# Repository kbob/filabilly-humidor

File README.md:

# FilaBilly Humidor

The FilaBilly Humidor (FBH) is a smart cabinet for 3D printer filament storage and humidity control.  It's based on an IKEA BILLY bookcase and contains an active dehumidifier.  It has lighting, environment sensors, and a display screen, and it is Internet enabled.

The FilaBilly Humidor is based on [ESPHome](https://esphome.io/).  It can be used as a standalone device or integrated into [Home Assistant](https://homeassistant.io/).

**Status:** Mostly vaporware.  Some materials have been acquired.

## FilaBilly Dehumidifier

The FilaBilly Dehumidifier (FBD) is the dehumidifier component.  It is a compact active dehumidifier that is also Internet enabled.  The FBD can also be used without the FBH, either standalone or directly integrated into Home Assistant.  The FBD also uses ESPHome.

**Status:** Designed, printed, tested.

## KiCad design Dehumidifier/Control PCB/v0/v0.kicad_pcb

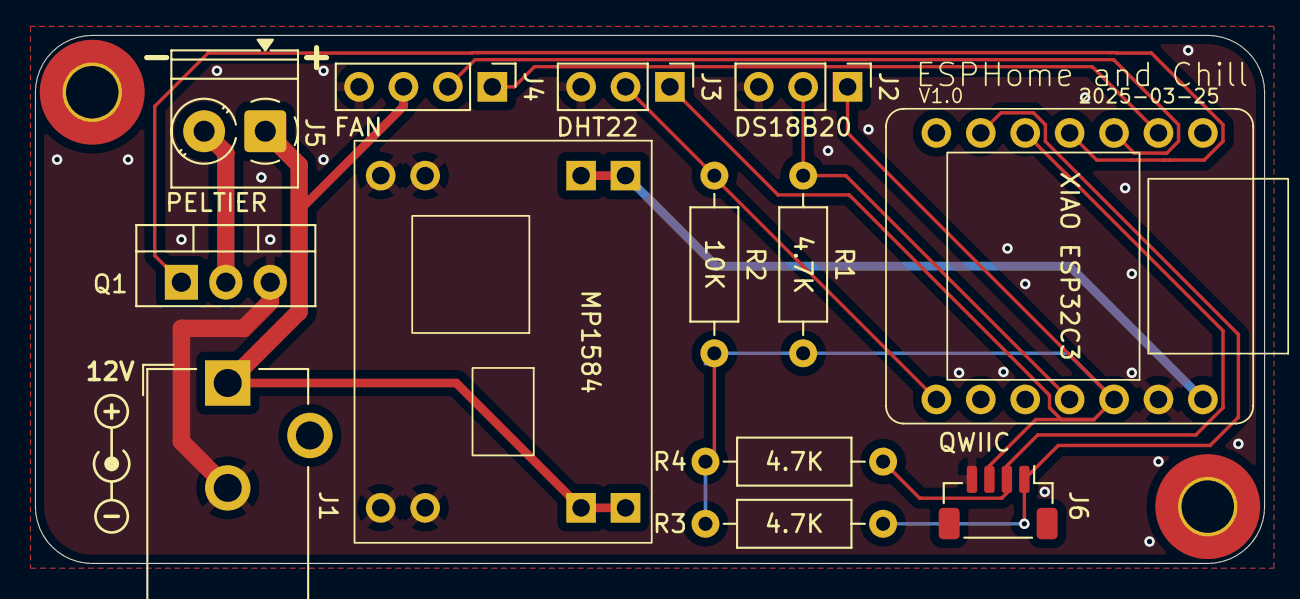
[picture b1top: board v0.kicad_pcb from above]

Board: 2 copper layers, 70.3 x 30.2 mm, 13 parts (0 on the bottom side), 12 nets.

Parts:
J1: Barrel_Jack; BarrelJack_CUI_PJ-102AH_Horizontal
J2, J3: 2.54mm Header; PinHeader_1x03_P2.54mm_Vertical
J4: 2.54mm Header; PinHeader_1x04_P2.54mm_Vertical
J5: Screw Term; TerminalBlock_Phoenix_PT-1,5-2-3.5-H_1x02_P3.50mm_Horizontal
J6: QWIIC; JST_SH_BM04B-SRSS-TB_1x04-1MP_P1.00mm_Vertical
Q1: IRLB8721PBF; TO-220-3_Vertical
R1, R3, R4: 4.7K; R_Axial_DIN0207_L6.3mm_D2.5mm_P10.16mm_Horizontal
R2: 10K; R_Axial_DIN0207_L6.3mm_D2.5mm_P10.16mm_Horizontal
U1: XIAO ESP32C3; XIAO_on_Sockets
U2: MP1584; MP1584_PCB

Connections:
+3.3V: J2.1, J3.1, J6.3, R1.1, R2.1, R3.1, R4.1, U1.12 (VCC_3V3)
+5V: U1.14 (VUSB), U2.7 (OUT+), U2.8 (OUT+)
+12V: J1.1, J4.3, J5.1, U2.1 (IN+), U2.2 (IN+)
GND: J1.2, J2.3, J3.3, J4.4, J6.4, Q1.3 (S), U1.13 (GND), U2.3 (IN-), U2.4 (IN-), U2.5 (OUT-), U2.6 (OUT-)
GPIO3/FAN_PWM: J4.1, U1.2 (D1)
GPIO4/FAN_TACH: J4.2, U1.3 (D2)
GPIO5/PELT: Q1.1 (G), U1.4 (D3)
GPIO6/SDA: J6.2, R4.2, U1.5 (D4)
GPIO7/SCL: J6.1, R3.2, U1.6 (D5)
GPIO10/COLD_TEMP: J2.2, R1.2, U1.11 (D10)
GPIO20/HUM: J3.2, R2.2, U1.8 (D7)
Peltier: J5.2, Q1.2 (D)

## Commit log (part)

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2025-03-27 Initial commit: dehumidifier control board v1.0
2025-04-16 Add revision V1.0 and date 3/25/2025 to schematic
2025-04-16 Rename dehumidifier control PCB to 'Control PCB/control-pcb'
2025-04-16 Commit V1.0 gerber ZIP file
2025-04-16 Move 'Control PCB/control-pcb' to control-pcb
2025-04-16 Add repository LICENSE and README
2025-04-20 First draft of the dehumidifier assembly guide
2025-04-20 Dehumidifier assembly guide is formatted. Still needs some photos.
2025-04-20 Add back cover to Assembly Guide
2025-04-20 Fix H1 spacing again
2025-04-24 First attempt at dehumidifier ESPHome configuration. Closely based on Ben Krejci's work. https://github.com/benkrejci/esphome
2025-04-24 Create .gitignore in ESPHome directory
2025-04-24 Reorganize ESPHome config, add control parameters
2025-04-24 Dehumidifier ESPHome config PID tuning and icon fix
    - removed PID controller derivative_averaging_samples
    - Chiller Temperature icon is now mdi:snowflake-thermometer
2025-04-26 Update Assembly Guide with more photos, better text and annotations
2025-04-28 Add printed files: .STL, .3mf, .f3d, and .STEP
2025-04-28 Minor edits to Assembly Guide
2025-12-27 Add control PCB schematic as PDF
2025-12-27 Add fan and surround STLs and images
